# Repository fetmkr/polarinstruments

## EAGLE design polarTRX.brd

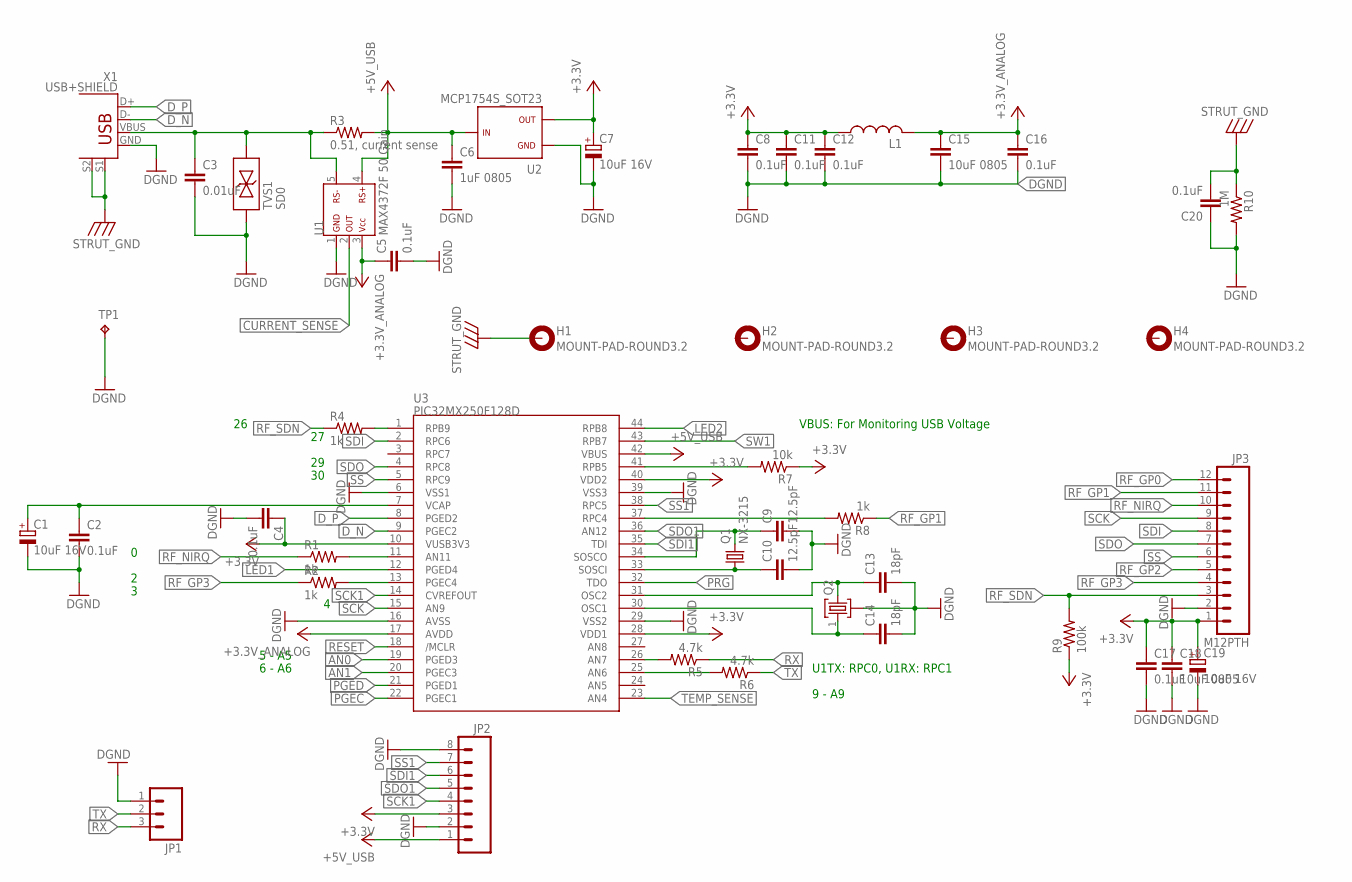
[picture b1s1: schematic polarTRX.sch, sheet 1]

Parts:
C1, C7, C19: 10uF 16V; C1206(3216)-A
C2, C4, C5, C8, C11, C12, C16, C17, C20: 0.1uF; C0603(1608)
C3: 0.01uF; C0603(1608)
C6: 1uF 0805; C0805(2012)
C9, C10: 12.5pF; C0603(1608)
C13, C14: 18pF; C0603(1608)
C15, C18: 10uF 0805; C0805(2012)
H1, H2, H3, H4: MOUNT-PAD-ROUND3.2; 3,2-PAD
JP1: M03PTH; 1X03
JP2: M08SILK_FEMALE_PTH; 1X08
JP3: M12PTH; 1X12
L1: L0805(2012)
Q1: NX-3215
Q2: CRYSTAL; HC_49US
R1, R2, R4, R8: 1k; R0603(1608)
R3: 0.51, current sense; R0805(2012)
R5, R6: 4.7k; R0603(1608)
R7: 10k; R0603(1608)
R9: 100k; R0603(1608)
R10: 1M; R0603(1608)
TP1: TP; TP-13
TVS1: SD0; SOD-323-NOPOL
U1: MAX4372F 50 Gain; SOT23-5DBV
U2: MCP1754S_SOT23; SOT23
U3: PIC32MX250F128D; TQFP44
X1: USB+SHIELD; USB-B-PTH

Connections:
+3.3V: C4.1, C7.1 (+), C8.1, C11.1, C12.1, C17.1, C18.1, C19.1 (+), JP2.3, JP3.1, L1.1, R7.1, R9.1, U2.2, U3.10 (VUSB3V3), U3.28 (VDD1), U3.40 (VDD2); also elsewhere on the board
+3.3V_ANALOG: C5.1, C15.1, C16.1, L1.2, U1.3, U3.17 (AVDD); also elsewhere on the board
+5V_USB: C6.1, JP2.1, R3.2, U1.4, U2.3, U3.42 (VBUS); also elsewhere on the board
AN0: U3.19 (PGED3); also elsewhere on the board
AN1: U3.20 (PGEC3); also elsewhere on the board
CURRENT_SENSE: U1.2; also elsewhere on the board
DGND: C1.2 (-), C2.2, C3.2, C4.2, C5.2, C6.2, C7.2 (-), C8.2, C9.2, C10.2, C11.2, C12.2, C13.2, C14.2, C15.2, C16.2, C17.2, C18.2, C19.2 (-), C20.1, JP1.1, JP2.2, JP2.8, JP3.2, Q2.2, R10.2, TP1.TP, TVS1.1, U1.1, U2.1, U3.6 (VSS1), U3.16 (AVSS), U3.29 (VSS2), U3.39 (VSS3), X1.GND; also elsewhere on the board
D_N: U3.9 (PGEC2), X1.D-
D_P: U3.8 (PGED2), X1.D+
LED1: U3.12 (PGED4); also elsewhere on the board
LED2: U3.44 (RPB8); also elsewhere on the board
unnamed: C13.1, Q2.3, U3.31 (OSC2)
unnamed: C1.1 (+), C2.1, U3.7 (VCAP)
unnamed: C14.1, Q2.1, U3.30 (OSC1)
unnamed: C3.1, R3.1, TVS1.2, U1.5, X1.VBUS
unnamed: R1.2, U3.11 (AN11)
unnamed: R2.2, U3.13 (PGEC4)
unnamed: C9.1, Q1.2, U3.34 (SOSCO)
unnamed: C10.1, Q1.1, U3.33 (SOSCI)
unnamed: R8.2, U3.37 (RPC4)
unnamed: R6.2, U3.25 (AN6)
unnamed: R5.2, U3.26 (AN7)
unnamed: R7.2, U3.41 (RPB5)
unnamed: R4.2, U3.1 (RPB9)
PGEC: U3.22 (PGEC1); also elsewhere on the board
PGED: U3.21 (PGED1); also elsewhere on the board
PRG: U3.32 (TDO); also elsewhere on the board
RESET: U3.18 (/MCLR); also elsewhere on the board
RF_GP0: JP3.12
RF_GP1: JP3.11, R8.1
RF_GP2: JP3.5
RF_GP3: JP3.4, R2.1
RF_NIRQ: JP3.10, R1.1
RF_SDN: JP3.3, R4.1, R9.2
RX: JP1.3, R5.1
SCK: JP3.9, U3.15 (AN9)
SCK1: JP2.4, U3.14 (CVREFOUT)
SDI: JP3.8, U3.2 (RPC6)
SDI1: JP2.6, U3.35 (TDI)
SDO: JP3.7, U3.4 (RPC8)
SDO1: JP2.5, U3.36 (AN12)
SS: JP3.6, U3.5 (RPC9)
SS1: JP2.7, U3.38 (RPC5)
STRUT_GND: C20.2, H1.B3,2, R10.1, X1.S1, X1.S2
SW1: U3.43 (RPB7); also elsewhere on the board
TEMP_SENSE: U3.23 (AN4); also elsewhere on the board
TX: JP1.2, R6.1

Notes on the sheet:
U1TX: RPC0, U1RX: RPC1
VBUS: For Monitoring USB Voltage
5 - A5
6 - A6
9 - A9

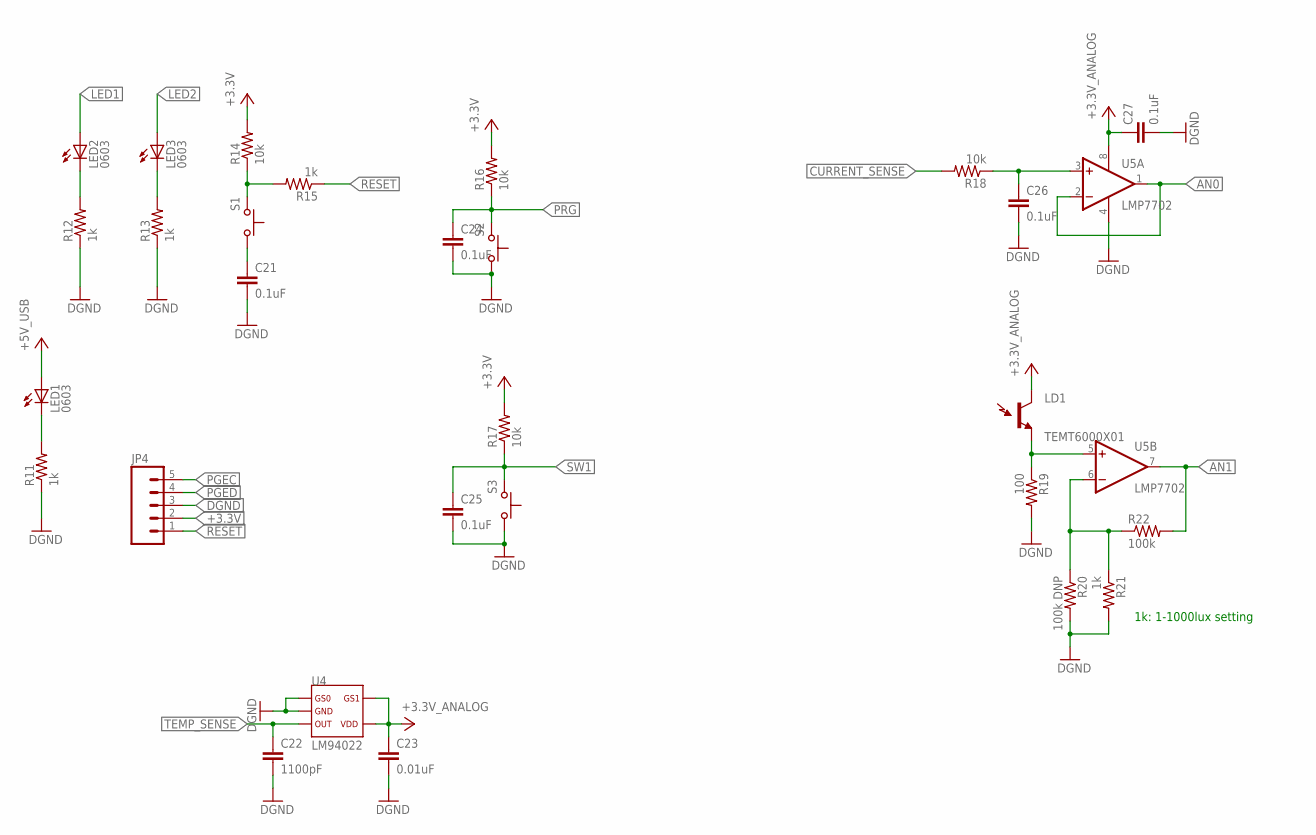
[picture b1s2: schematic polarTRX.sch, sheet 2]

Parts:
C21, C24, C25, C26, C27: 0.1uF; C0603(1608)
C22: 1100pF; C0603(1608)
C23: 0.01uF; C0603(1608)
JP4: M05PTH; 1X05
LD1: TEMT6000X01; TEMT6000-SEN
LED1, LED2, LED3: 0603; LED-0603
R11, R12, R13, R15, R21: 1k; R0603(1608)
R14, R16, R17, R18: 10k; R0603(1608)
R19: 100; R0603(1608)
R20: 100k DNP; R0603(1608)
R22: 100k; R0603(1608)
S1, S2, S3: SWITCH; SKHLACA010
U4: LM94022; SC70-5
U5: LMP7702; DGK_S-DPSO-G8

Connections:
+3.3V: JP4.2, R14.2, R16.2, R17.2; also elsewhere on the board
+3.3V_ANALOG: C23.1, C27.1, LD1.COLLECTOR (C1), U4.4, U4.5, U5.8 (V+); also elsewhere on the board
+5V_USB: LED1.A; also elsewhere on the board
AN0: U5.1 (OUT), U5.2 (-IN); also elsewhere on the board
AN1: R22.2, U5.7 (OUT); also elsewhere on the board
CURRENT_SENSE: R18.2; also elsewhere on the board
DGND: C21.2, C22.2, C23.2, C24.2, C25.2, C26.2, C27.2, JP4.3, R11.1, R12.1, R13.1, R19.2, R20.2, R21.2, S2.P$2, S3.P$2, U4.1, U4.2, U5.4 (V-); also elsewhere on the board
LED1: LED2.A; also elsewhere on the board
LED2: LED3.A; also elsewhere on the board
unnamed: R14.1, R15.2, S1.P$1
unnamed: C21.1, S1.P$2
unnamed: LED1.C, R11.2
unnamed: LED2.C, R12.2
unnamed: LED3.C, R13.2
unnamed: C26.1, R18.1, U5.3 (+IN)
unnamed: LD1.EMITTER (E1), R19.1, U5.5 (+IN)
unnamed: R20.1, R21.1, R22.1, U5.6 (-IN)
PGEC: JP4.5; also elsewhere on the board
PGED: JP4.4; also elsewhere on the board
PRG: C24.1, R16.1, S2.P$1; also elsewhere on the board
RESET: JP4.1, R15.1; also elsewhere on the board
SW1: C25.1, R17.1, S3.P$1; also elsewhere on the board
TEMP_SENSE: C22.1, U4.3; also elsewhere on the board

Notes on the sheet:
1k: 1-1000lux setting

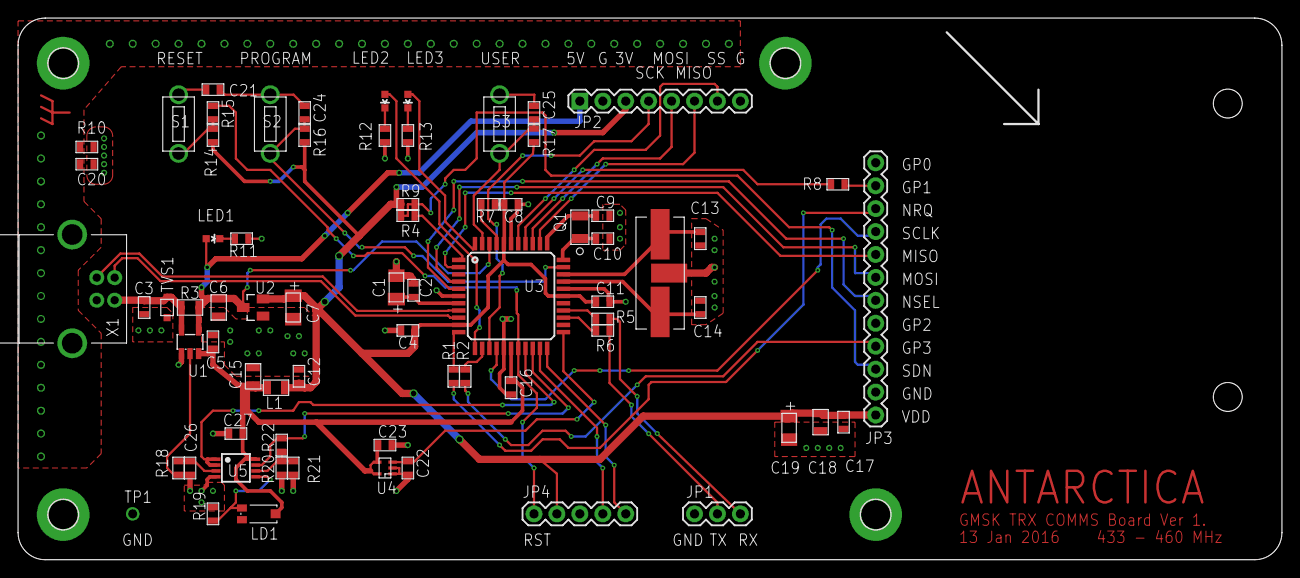
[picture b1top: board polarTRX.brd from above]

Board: 2 copper layers, 140.0 x 60.0 mm, 75 parts (0 on the bottom side), 53 nets.

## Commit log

2016-01-06 :confetti_ball: Added .gitattributes
2016-01-06 first
2016-01-06 some parts added
2016-01-10 parts added
2016-01-12 temt 6000
2016-01-13 schematic almost done
2016-01-13 board layout done
2016-01-15 gerber file added

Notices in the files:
parts and their libraries:
SparkFun-Connectors: Licensing: Creative Commons ShareAlike 4.0 International - https://creativecommons.org/licenses/by-sa/4.0
SparkFun: Licensing: CC v3.0 Share-Alike You are welcome to use this library for commercial purposes.
